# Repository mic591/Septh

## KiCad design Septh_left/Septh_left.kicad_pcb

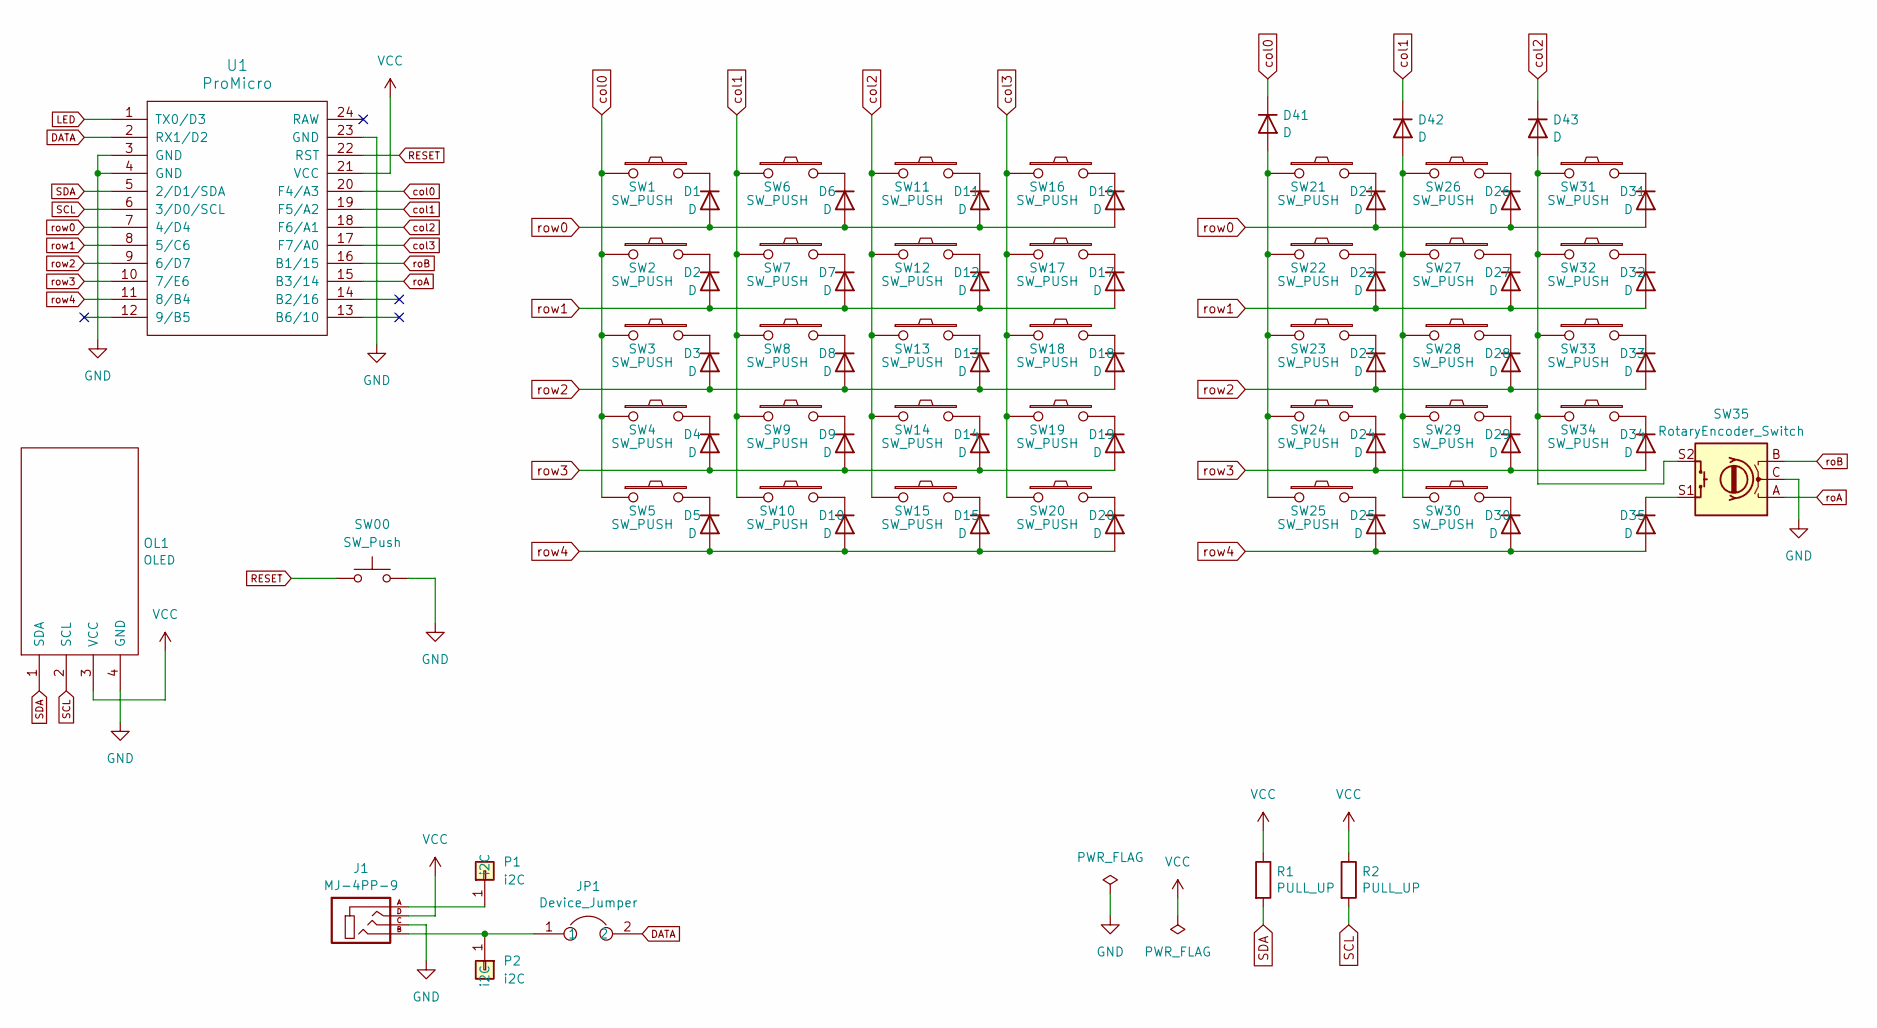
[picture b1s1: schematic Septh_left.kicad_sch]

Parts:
D1, D2, D3, D4, D5, D6, D7, D8, D9, D10, D11, D12, D13, D14, D15, D16, D17, D18, D19, D20, D21, D22, D23, D24, D25, D26, D27, D28, D29, D30, D31, D32, D33, D34, D35, D41, D42, D43: D; Diode_SMD_top
J1: MJ-4PP-9; TRRS_MJ-4PP-9
JP1: Device_Jumper; jamper
OL1: OLED
P1, P2: i2C; i2C_1pin
R1, R2: PULL_UP; R_0603_1608Metric
SW00: SW_Push; ResetSW
SW1, SW2, SW3, SW4, SW5, SW6, SW7, SW8, SW9, SW10, SW11, SW12, SW13, SW14, SW15, SW16, SW17, SW18, SW19, SW20, SW21, SW22, SW23, SW24, SW25, SW26, SW27, SW28, SW29, SW30, SW31, SW32: SW_PUSH; Choc_v2_Hotswap_1u_Narrow
SW33, SW34: SW_PUSH; Choc_v2_予備配線
SW35: RotaryEncoder_Switch; RotaryEncoder_EC12E
U1: ProMicro; Micon_ProMicro

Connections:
DATA: JP1.2, U1.2 (RX1/D2)
GND: J1.C, OL1.4 (GND), SW00.2, SW35.C, U1.3 (GND), U1.4 (GND), U1.23 (GND)
LED: U1.1 (TX0/D3)
unnamed: D1.1 (K), SW1.2
unnamed: D2.1 (K), SW2.2
unnamed: D3.1 (K), SW3.2
unnamed: D4.1 (K), SW4.2
unnamed: D5.1 (K), SW5.2
unnamed: D6.1 (K), SW6.2
unnamed: D7.1 (K), SW7.2
unnamed: D8.1 (K), SW8.2
unnamed: D9.1 (K), SW9.2
unnamed: D10.1 (K), SW10.2
unnamed: D11.1 (K), SW11.2
unnamed: D12.1 (K), SW12.2
unnamed: D13.1 (K), SW13.2
unnamed: D14.1 (K), SW14.2
unnamed: D15.1 (K), SW15.2
unnamed: D16.1 (K), SW16.2
unnamed: D17.1 (K), SW17.2
unnamed: D18.1 (K), SW18.2
unnamed: D19.1 (K), SW19.2
unnamed: D20.1 (K), SW20.2
unnamed: D21.1 (K), SW21.2
unnamed: D22.1 (K), SW22.2
unnamed: D23.1 (K), SW23.2
unnamed: D24.1 (K), SW24.2
unnamed: D25.1 (K), SW25.2
unnamed: D26.1 (K), SW26.2
unnamed: D27.1 (K), SW27.2
unnamed: D28.1 (K), SW28.2
unnamed: D29.1 (K), SW29.2
unnamed: D30.1 (K), SW30.2
unnamed: D31.1 (K), SW31.2
unnamed: D32.1 (K), SW32.2
unnamed: D33.1 (K), SW33.2
unnamed: D34.1 (K), SW34.2
unnamed: D35.1 (K), SW35.S1
unnamed: D41.2 (A), SW21.1, SW22.1, SW23.1, SW24.1, SW25.1
unnamed: D42.2 (A), SW26.1, SW27.1, SW28.1, SW29.1, SW30.1
unnamed: D43.2 (A), SW31.1, SW32.1, SW33.1, SW34.1, SW35.S2
unnamed: J1.A, P1.1 (i2C)
unnamed: J1.B, JP1.1, P2.1 (i2C)
RESET: SW00.1, U1.22 (RST)
SCL: OL1.2 (SCL), R2.2, U1.6 (3/D0/SCL)
SDA: OL1.1 (SDA), R1.2, U1.5 (2/D1/SDA)
VCC: J1.D, OL1.3 (VCC), R1.1, R2.1, U1.21 (VCC)
col0: D41.1 (K), SW1.1, SW2.1, SW3.1, SW4.1, SW5.1, U1.20 (F4/A3)
col1: D42.1 (K), SW6.1, SW7.1, SW8.1, SW9.1, SW10.1, U1.19 (F5/A2)
col2: D43.1 (K), SW11.1, SW12.1, SW13.1, SW14.1, SW15.1, U1.18 (F6/A1)
col3: SW16.1, SW17.1, SW18.1, SW19.1, SW20.1, U1.17 (F7/A0)
roA: SW35.A, U1.15 (B3/14)
roB: SW35.B, U1.16 (B1/15)
row0: D1.2 (A), D6.2 (A), D11.2 (A), D16.2 (A), D21.2 (A), D26.2 (A), D31.2 (A), U1.7 (4/D4)
row1: D2.2 (A), D7.2 (A), D12.2 (A), D17.2 (A), D22.2 (A), D27.2 (A), D32.2 (A), U1.8 (5/C6)
row2: D3.2 (A), D8.2 (A), D13.2 (A), D18.2 (A), D23.2 (A), D28.2 (A), D33.2 (A), U1.9 (6/D7)
row3: D4.2 (A), D9.2 (A), D14.2 (A), D19.2 (A), D24.2 (A), D29.2 (A), D34.2 (A), U1.10 (7/E6)
row4: D5.2 (A), D10.2 (A), D15.2 (A), D20.2 (A), D25.2 (A), D30.2 (A), D35.2 (A), U1.11 (8/B4)

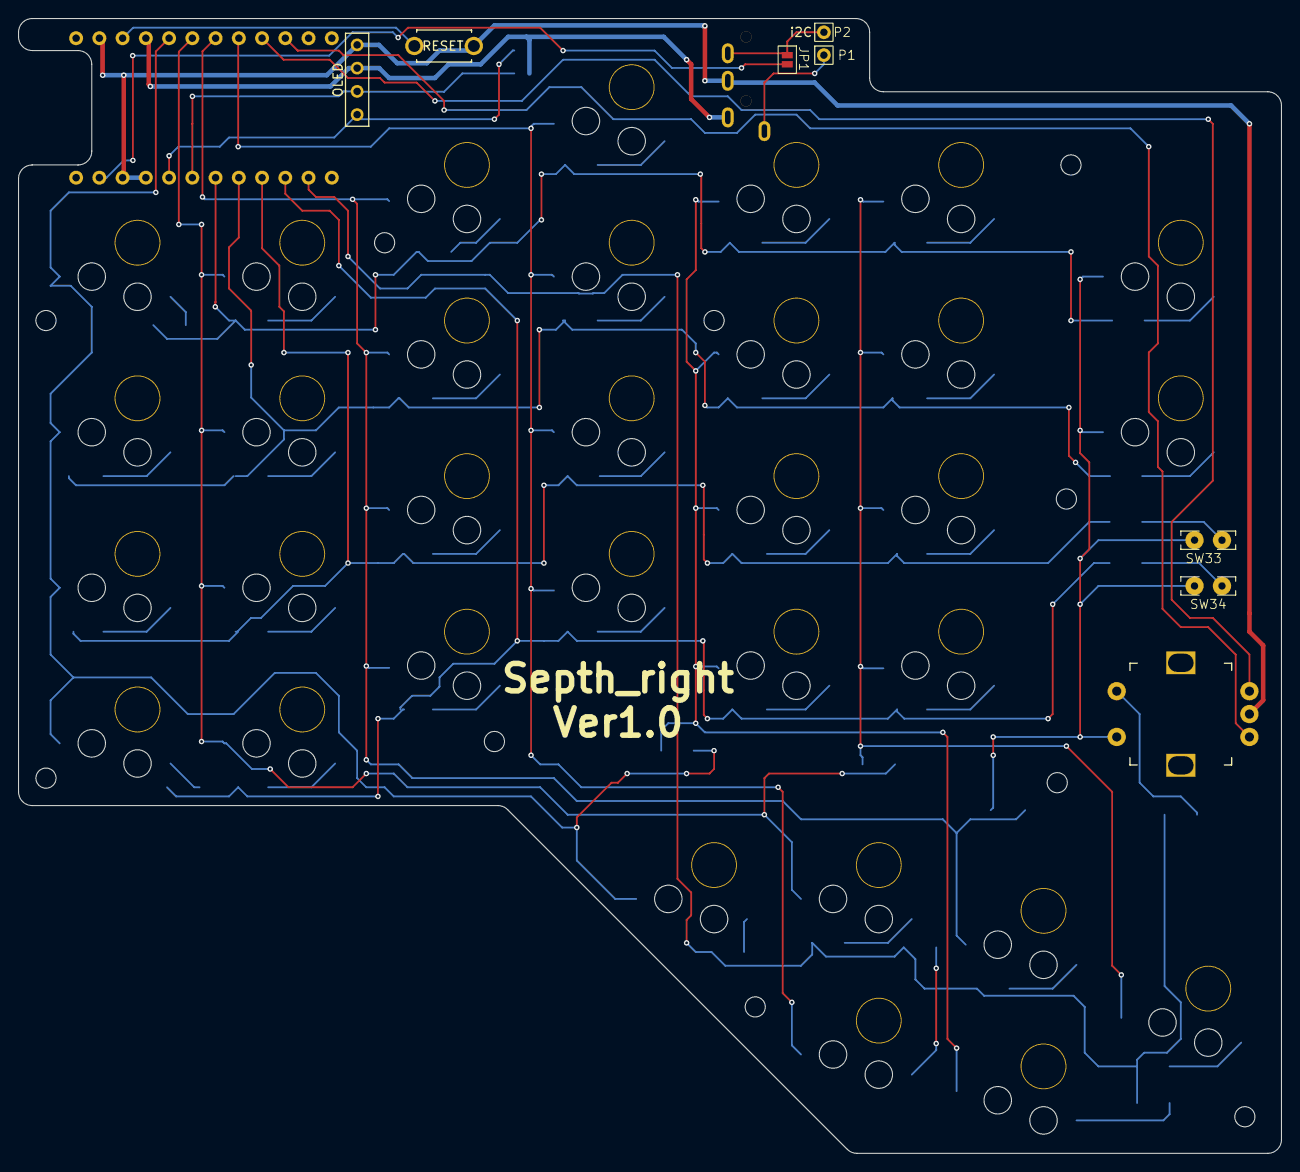
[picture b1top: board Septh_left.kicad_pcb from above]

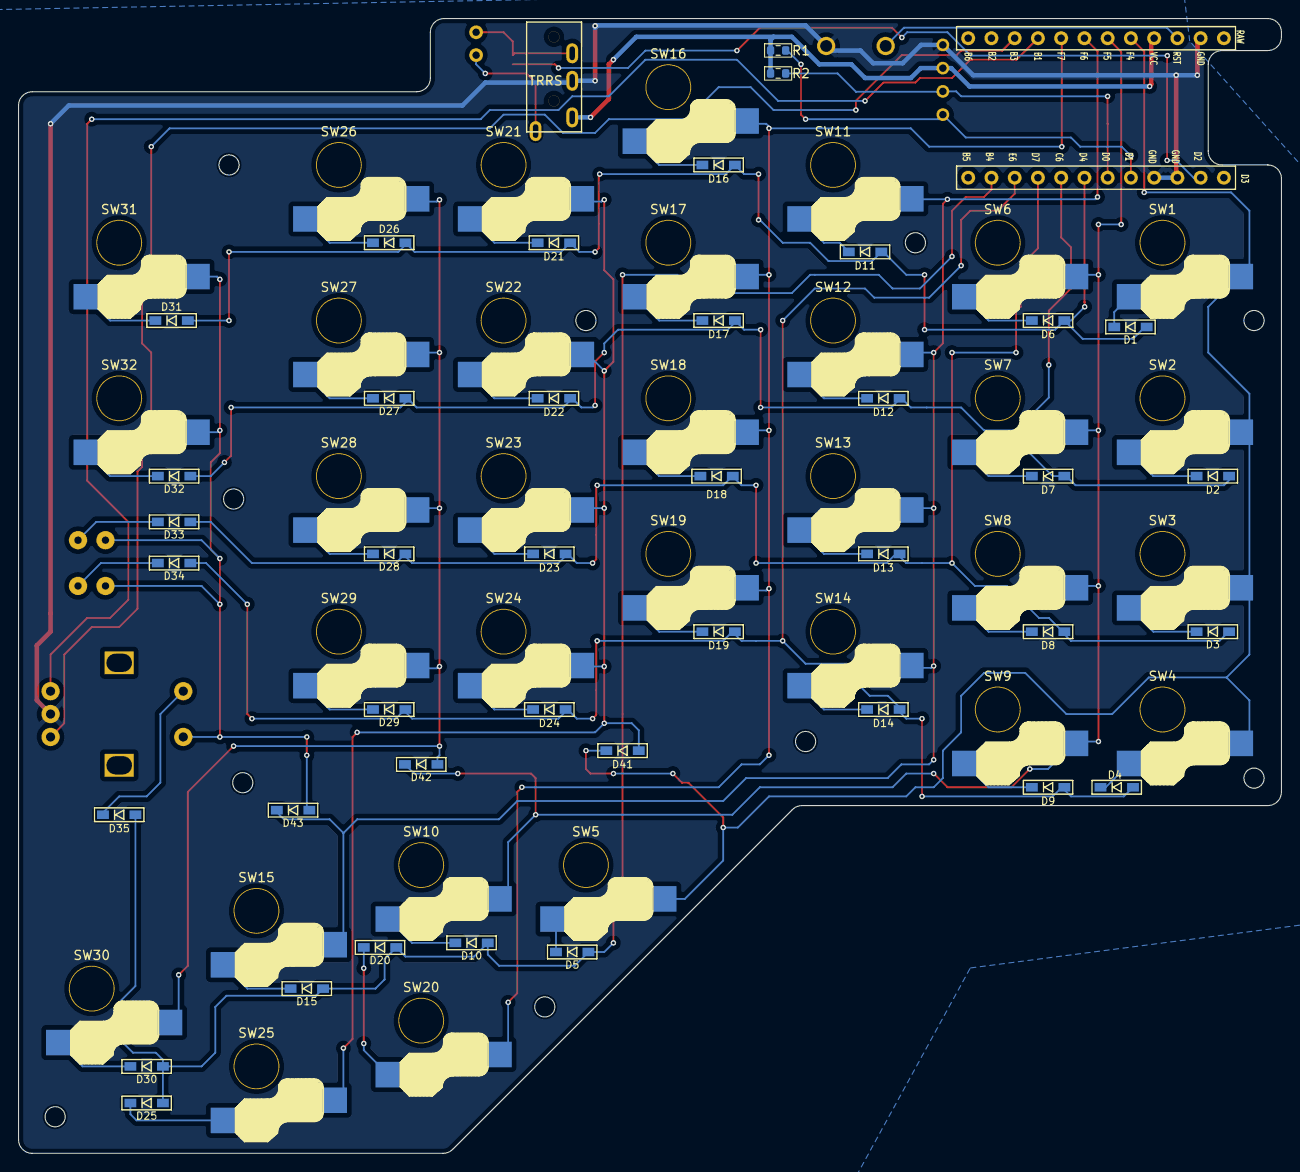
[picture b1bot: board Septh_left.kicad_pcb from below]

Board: 2 copper layers, 138.0 x 124.0 mm, 92 parts (74 on the bottom side), 57 nets.

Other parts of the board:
Ref**: Val**; m2_Screw_Hole
Ref**#2, Ref**#3, Ref**#4, Ref**#5, Ref**#6, Ref**#7, Ref**#8, Ref**#9, Ref**#10: Val**; m2_Screw_Hole
